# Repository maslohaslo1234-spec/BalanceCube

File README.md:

# BalanceCube

---

## What is this?

It's a 3D printed cube that can (hopefully) balance on one corner or one edge. It uses flywheels, brushless motors, an ESP32, and an IMU to balance the cube.

### Features:
- **Balancing** - using three brushless motors and flywheels.
- **Custom PCB** - Designed in KiCad.
- **Lightweight Frame** - It can almost fly (:
- **Firmware** - It works (optional).

---

## How it works?

It works by spinning the reaction wheels in the opposite way that the cube is tilting. The reaction wheels are spun by brushless motors, and the motors are controlled by the ESP32. The ESP32 gets data from the MPU6050 IMU and processes this data using my code, and then it sends control signals to the motors. This way the cube always stays upright (hopefully).

---

## Why am I making this?

I stumbled upon the Fallen program and started thinking if I would be able to join. I remembered a recent YT video from [The Tinkering Techie channel](https://www.youtube.com/@TheTinkeringTechie) about a balancing cube and thought that it was really cool and that I can make something similar in Fallen.

---

## Mechanical Design

The mechanical parts are modeled in Onshape.

Public Onshape Project Link: [Onshape BalanceCube Document](https://cad.onshape.com/documents/2c01e583674b5bc36f37b82b/w/a163e07f377434656225f53e/e/8aebbe53c625277084c7079e?renderMode=0&uiState=6af1ee5f03c2db71e7140d83)

In the repo it can be found here: [CAD](cad/)

---

## Electronics

The PCB is designed in KiCad.

In the repo it can be found here: [PCB](PCB/)

---

## Bill of Materials (BOM)

All parts, links, and prices can be found in [bom.csv](bom.csv).

---

## Inspirations & Credits

- [Rem-RC Self-Balancing-Cube](https://github.com/remrc/Self-Balancing-Cube)
- [ETH Zurich Cubli](https://idsc.ethz.ch/research-dandrea/research-projects/archive/cubli.html)
- [The Tinkering Techie](https://www.youtube.com/@TheTinkeringTechie)

---

## License

This project is open-source and licensed under the [MIT License](LICENSE).

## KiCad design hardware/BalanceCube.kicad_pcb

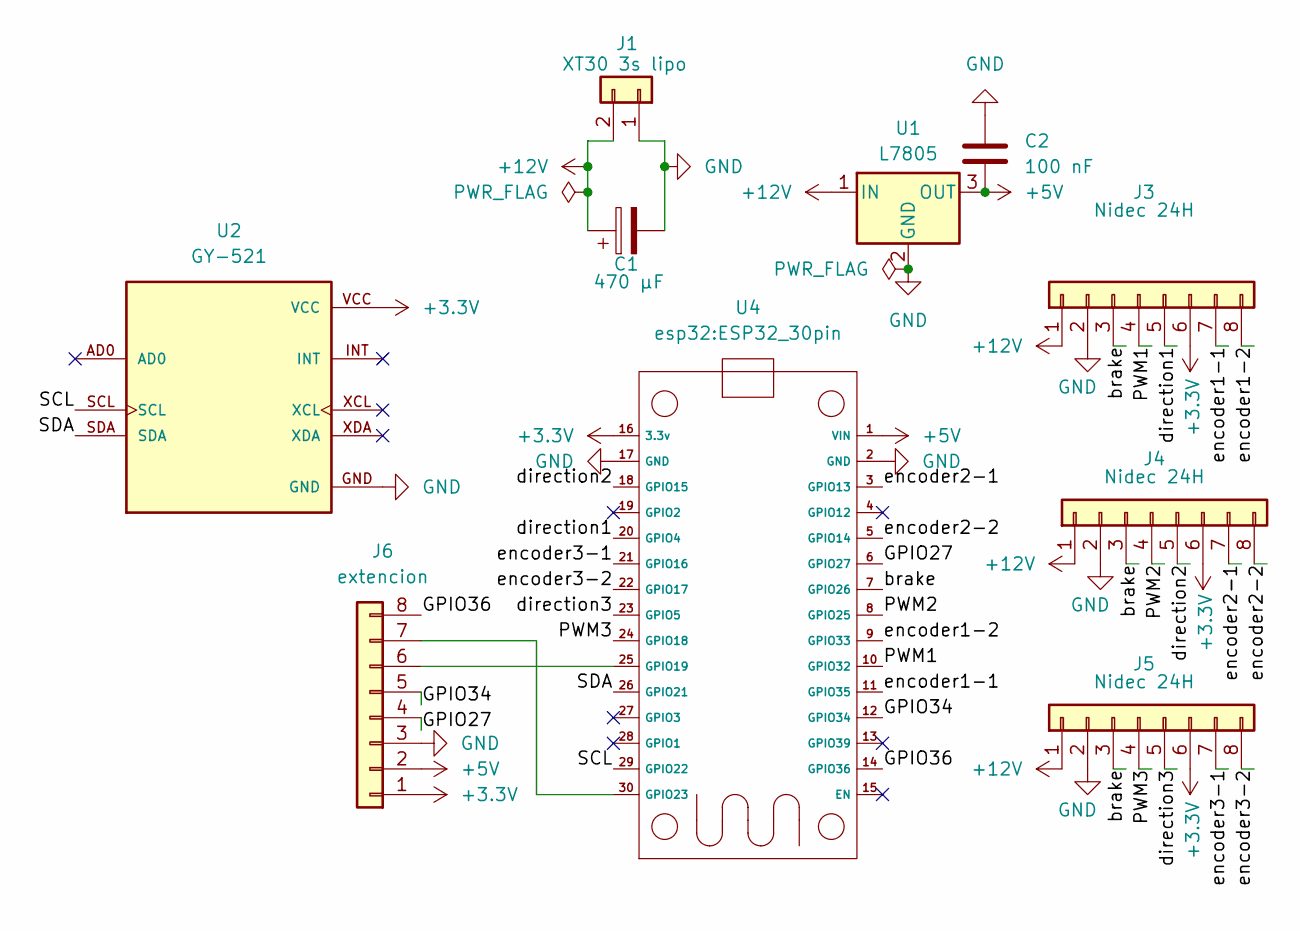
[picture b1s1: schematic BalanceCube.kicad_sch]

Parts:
C1: 470 µF; CP_Radial_D10.0mm_P5.00mm
C2: 100 nF; C_Disc_D5.0mm_W2.5mm_P5.00mm
J1: XT30 3s lipo; AMASS_XT30PW-M_1x02_P2.50mm_Horizontal
J3, J4, J5: Nidec 24H; JST_PH_B8B-PH-K_1x08_P2.00mm_Vertical
J6: extencion; PinHeader_1x08_P2.54mm_Vertical
U1: L7805; TO-220-3_Vertical
U2: GY-521; MODULE_GY-521; PARTREV NA
U4: ESP32_30pin

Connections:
+3.3V: J3.6, J4.6, J5.6, J6.1, U2.VCC, U4.16 (3.3v)
+5V: C2.2, J6.2, U1.3 (OUT), U4.1 (VIN)
+12V: C1.1, J1.2, J3.1, J4.1, J5.1, U1.1 (IN)
/GPIO27: J6.4, U4.6 (GPIO27)
/GPIO34: J6.5, U4.12 (GPIO34)
/GPIO36: J6.8, U4.14 (GPIO36)
/PWM1: J3.4, U4.10 (GPIO32)
/PWM2: J4.4, U4.8 (GPIO25)
/PWM3: J5.4, U4.24 (GPIO18)
/SCL: U2.SCL, U4.29 (GPIO22)
/SDA: U2.SDA, U4.26 (GPIO21)
/brake: J3.3, J4.3, J5.3, U4.7 (GPIO26)
/direction1: J3.5, U4.20 (GPIO4)
/direction2: J4.5, U4.18 (GPIO15)
/direction3: J5.5, U4.23 (GPIO5)
/encoder1-1: J3.7, U4.11 (GPIO35)
/encoder1-2: J3.8, U4.9 (GPIO33)
/encoder2-1: J4.7, U4.3 (GPIO13)
/encoder2-2: J4.8, U4.5 (GPIO14)
/encoder3-1: J5.7, U4.21 (GPIO16)
/encoder3-2: J5.8, U4.22 (GPIO17)
GND: C1.2, C2.1, J1.1, J3.2, J4.2, J5.2, J6.3, U1.2 (GND), U2.GND, U4.2 (GND), U4.17 (GND)
unnamed: J6.6, U4.25 (GPIO19)
unnamed: J6.7, U4.30 (GPIO23)

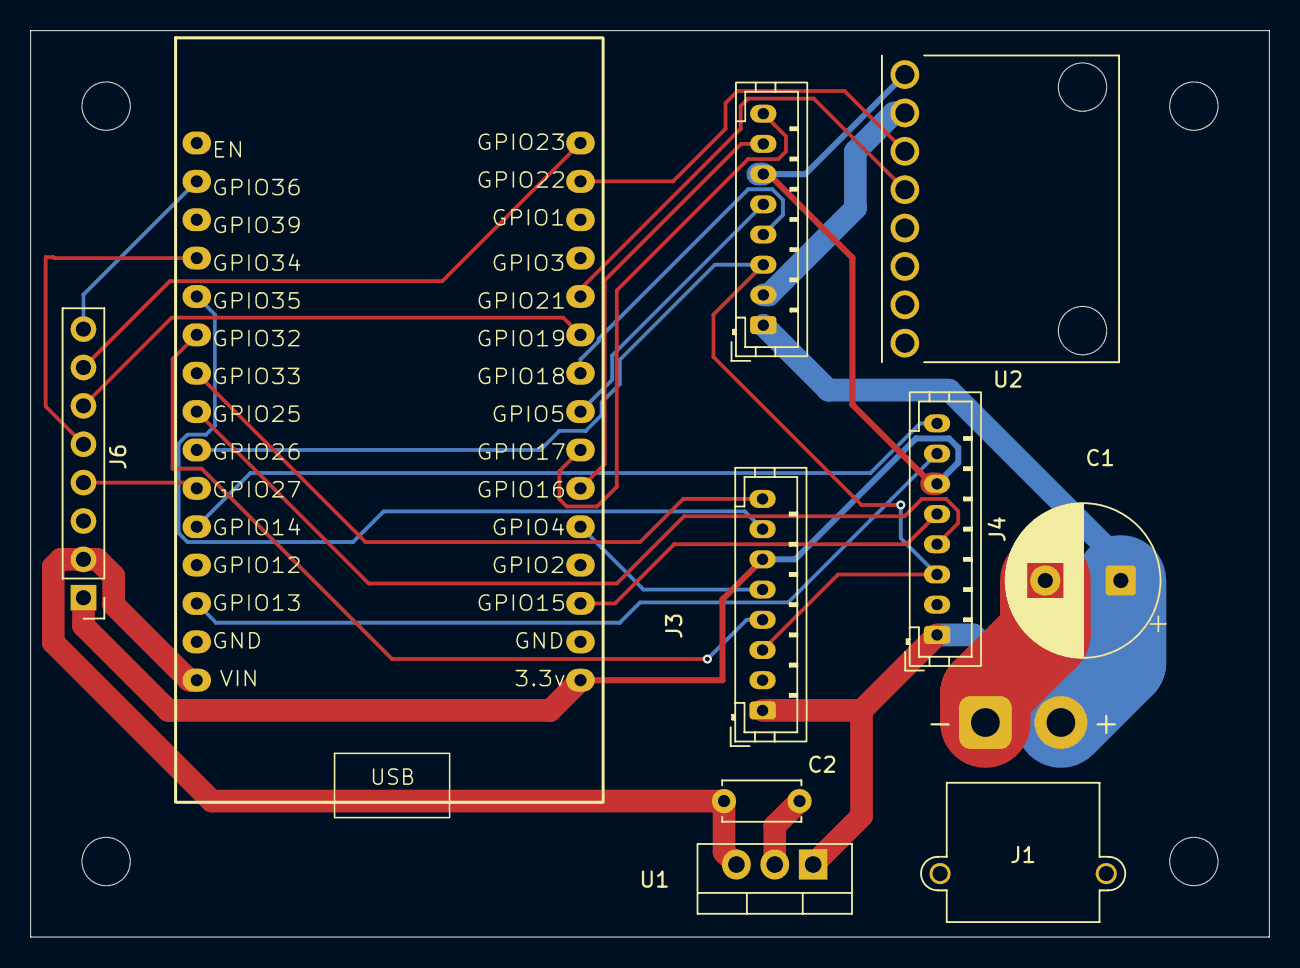
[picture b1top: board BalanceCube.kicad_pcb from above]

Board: 2 copper layers, 82.0 x 60.0 mm, 10 parts (0 on the bottom side), 24 nets.
